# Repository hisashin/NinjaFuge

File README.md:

NinjaFuge
==========

Opensource ([CC BY-NC-SA 2.5](https://creativecommons.org/licenses/by-nc-sa/2.5/)) centrifuge with cover sensor and lock. Derived from [F.Lab's one](http://www.instructables.com/id/3D-Printed-DIYbio-Mini-Centrifuge/).

- [Frequently asked questions](#faq)
- [Changelog](#change)
- [Please note before making](#note)
- [Bill of material](#bom)
- [Wirings](#wire)
- [Source code](https://github.com/hisashin/NinjaFuge/blob/master/sourcecode/NinjaFuge/NinjaFuge.ino)
- [Assembly instructions](#assembly)

### FAQ

- How much?

	I made at $20 from junks. If you buy everythings new in Japan, total parts price is $75 now.

- How fast?

	Max 12,000RPM in my case by connecting 12V adapter to cheapest ($10) 1000KV (that means +1000RPM per 1V) motor. You can make it faster if you use higher voltage, faster motor or enough ampere. Do not exceed absolute maximum voltages of motor, ESC and microcontroller.

### Changelog

- 2017 Aug 7 : Changes from [F.Lab's one](http://www.instructables.com/id/3D-Printed-DIYbio-Mini-Centrifuge/)
	- Enclosure is changed from 3d printing to acrylic lasercut. because I think printing takes too long time and easier to get fail.
	- Added magnet to cover and reed switch to base. so that it can stop rorating when cover is opened.
- 2017 Aug 8 : Add safety lock
	- I don't know how to brake motor and it takes seconds to stop rorating. That means it's still not safe perfectly. 
	Small servo motor should be added to lock the cover while rotating.

### Notes before making

- Any hinge around you can be used but yours will not be same as mine. Don't forget to change holes on both cover_back and base_back to yours.
- Similar minor changes will be required for other parts like motor, variable resistor and switch. If you use bigger Arduino, basement should be wider.
- I used acrylic board, polycarbonate screws and nuts. If you want to proof it against rotor break, polycarbonate board, steel screws and [nylon nuts](https://en.wikipedia.org/wiki/Nyloc_nut) are recommended.

### Bill of material

- Lasercut 3mm acrylic or polycarbonate parts with [this](https://github.com/hisashin/NinjaFuge/blob/master/lasercut/NinjaFuge_3mm_clear.pdf).
- 3d printed [rotor](https://github.com/hisashin/NinjaFuge/blob/master/3dprint/stl/NinjaFuge_F.lab_Rotor.stl) and [motor base](https://github.com/hisashin/NinjaFuge/blob/master/3dprint/stl/NinjaFuge_motor_holder.stl) with any material.
- Some heat shrinkable tubes with different diameters are useful to protect solderings.
- Small microcontroller like [Arduino Nano](https://store.arduino.cc/usa/arduino-nano) ($22), [Arduino Pro Mini](http://www.sparkfun.com/products/11113) ($10) or anything you like. If you can make Arduino with [Arduino](https://www.arduino.cc/en/Tutorial/ArduinoISP) or [AVRISP mkII](http://www.atmel.com/tools/avrispmkii.aspx), single [ATmega328](https://www.digikey.jp/product-detail/ja/microchip-technology/ATMEGA328P-PU/ATMEGA328P-PU-ND/1914589) ($2.2) is enough. In any case, these pins are required.
	- 1 analog input for tune
	- 1 digital input to catch [interrupt](https://www.arduino.cc/en/Reference/AttachInterrupt) of reed switch
	- 2 digital output for ESC and door lock servo. VCC should be connected to them too. Refer [Wirings](#wire).
- Parts for enclosure
	- 29 M3 10mm screws
	- 8 M3 nuts
	- 4 M3 25mm spacer (both female) for base
	- 3 M3 100mm spacer (both female) for cover
	- To hold door lock servo, I used
		- 2 M2 8mm screws
		- 2 M2 nuts

- Are you living in Japan as me? Good. No need to change lasercut design if you use them.

	- [Brushless motor and ESC kit](https://www.amazon.co.jp/gp/product/B01MTCBO7D/ref=oh_aui_detailpage_o09_s00?ie=UTF8&psc=1)
	- [Small servo to lock door]()
	- [Variable resistor](http://akizukidenshi.com/catalog/g/gP-00246/)
	- [Nob for resistor](http://akizukidenshi.com/catalog/g/gP-00246/)
	- [Single circuit locker switch](https://www.sengoku.co.jp/mod/sgk_cart/detail.php?code=3A8K-4BFY)
	- [Neodymium magnet](http://www.sengoku.co.jp/mod/sgk_cart/detail.php?code=EEHD-4VZZ)
	- [Reed switch](http://akizukidenshi.com/catalog/g/gP-03676/)
	- [Hinge](https://hands.net/goods/4991807041906/)
	- [4 rubber foot if you want](http://www.sengoku.co.jp/mod/sgk_cart/detail.php?code=6AZE-JELC)
	- [DC jack](http://www.sengoku.co.jp/mod/sgk_cart/detail.php?code=EEHD-0HMZ)
	- [12V AC adapter](http://akizukidenshi.com/catalog/g/gM-06961/)
		- 5A looks well. 1A wasn't enough. If you need maximum RPM, check how much ampere your ESC needs.

- If not, it would be cheaper to find items similar to above list around you and move [holes](https://github.com/hisashin/NinjaFuge/blob/master/lasercut/NinjaFuge_3mm_clear.pdf) a little for each of them.

### Wirings

### Assembly instructions

- Need to make latest model from scratch taking photos or movies to document here. Anyone want to do that?

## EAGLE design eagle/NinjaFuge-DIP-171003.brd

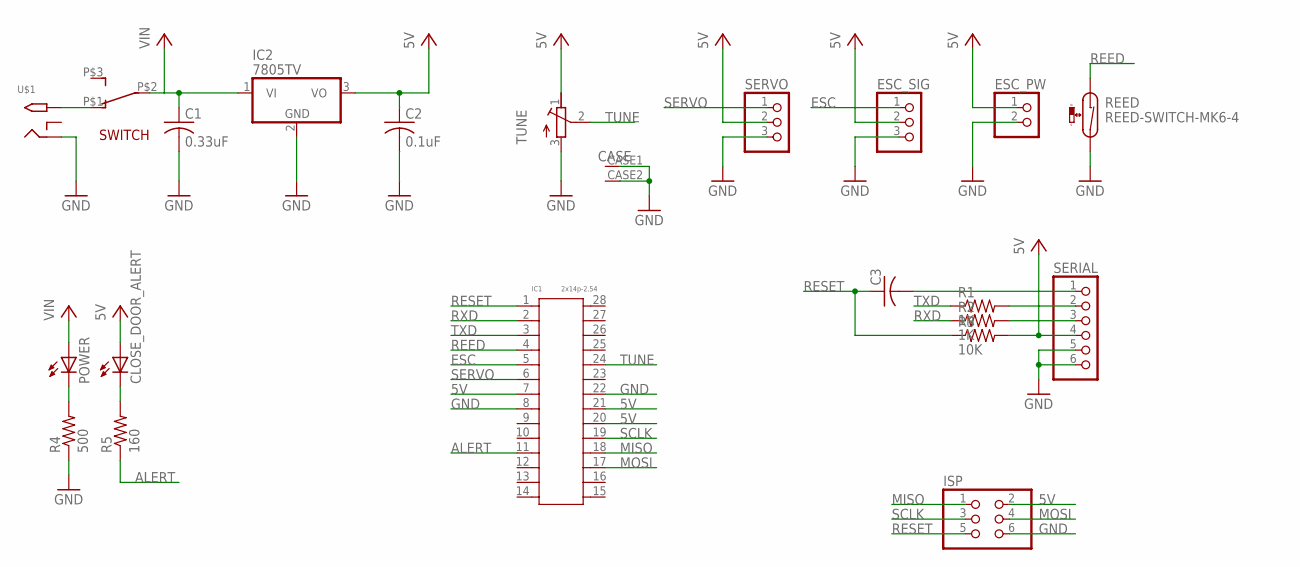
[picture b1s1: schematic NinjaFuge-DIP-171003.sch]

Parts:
C1: 0.33uF; C050-024X044
C2: 0.1uF; C050-024X044
C3: C-US050-024X044; C050-024X044
CLOSE_DOOR_ALERT: LED3MM
ESC_PW: PINHD-1X2; 1X02
ESC_SIG: PINHD-1X3; 1X03
IC1: 2x14p-2.54; SCK28-2.54-35.6X10MM
IC2: 7805TV; TO220V
ISP: PINHD-2X3; 2X03
POWER: LED3MM
R1, R2: 1K; 0204/5
R3: 10K; 0204/5
R4: 500; 0204/5
R5: 160; 0204/5
REED: REED-SWITCH-MK6-4; MK6-4
SERIAL: PINHD-1X6; 1X06
SERVO: PINHD-1X3; 1X03
SWITCH: MARUSHIN_MSR5
TUNE: RK09D117000B
U$1: 2.1MMJACKTHM; PJ-102A

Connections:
5V: C2.1, CLOSE_DOOR_ALERT.A, ESC_SIG.2, IC1.7, IC1.20, IC1.21, IC2.3 (VO), ISP.2, R3.2, SERIAL.4, SERVO.2, TUNE.1
ALERT: IC1.11, R5.1
ESC: ESC_SIG.1, IC1.5
GND: C1.2, C2.2, ESC_PW.2, ESC_SIG.3, IC1.8, IC1.22, IC2.2 (GND), ISP.6, R4.1, REED.2, SERIAL.5, SERIAL.6, SERVO.3, TUNE.3, TUNE.CASE1, TUNE.CASE2, U$1.RING
MISO: IC1.18, ISP.1
MOSI: IC1.17, ISP.4
unnamed: SWITCH.P$1 (1), U$1.TIP
unnamed: R2.2, SERIAL.3
unnamed: R1.2, SERIAL.2
unnamed: POWER.K (C), R4.2
unnamed: C3.2, SERIAL.1
unnamed: CLOSE_DOOR_ALERT.K (C), R5.2
REED: IC1.4, REED.1
RESET: C3.1, IC1.1, ISP.5, R3.1
RXD: IC1.2, R2.1
SCLK: IC1.19, ISP.3
SERVO: IC1.6, SERVO.1
TUNE: IC1.24, TUNE.2
TXD: IC1.3, R1.1
VIN: C1.1, ESC_PW.1, IC2.1 (VI), POWER.A, SWITCH.P$2 (2)

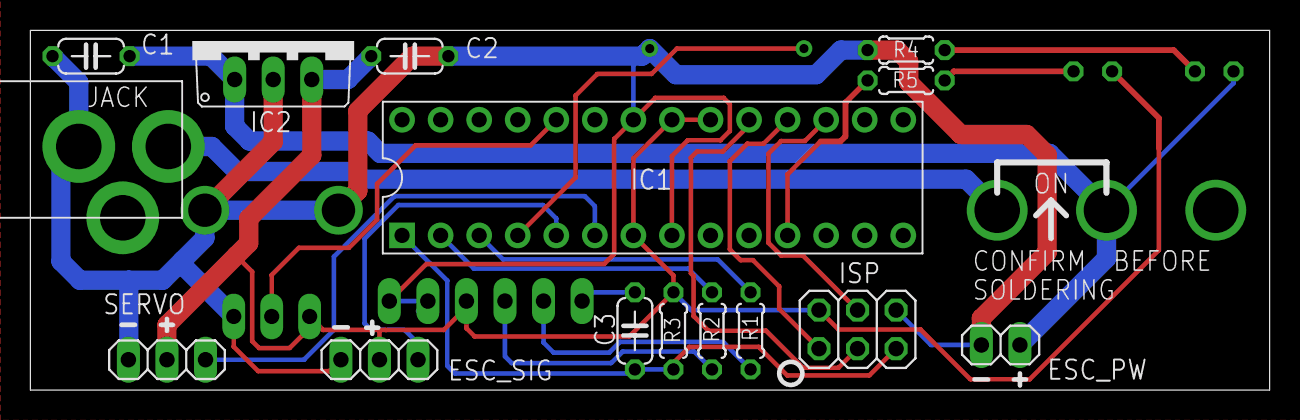
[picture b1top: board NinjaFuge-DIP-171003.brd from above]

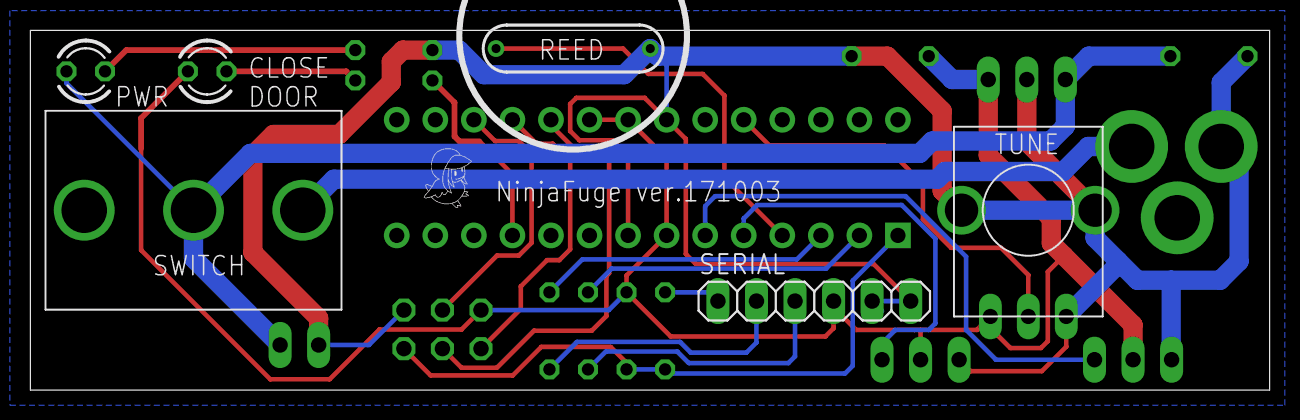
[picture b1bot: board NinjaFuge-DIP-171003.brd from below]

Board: 2 copper layers, 81.7 x 23.7 mm, 22 parts (7 on the bottom side), 20 nets.

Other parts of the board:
U$2: TORI_0.125

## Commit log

2017-08-07 move dir
2017-08-07 add diagram
2017-08-07 update diagram
2017-08-07 door lock added
2017-08-08 update md
2017-08-09 update lasercut
2017-08-09 update markdown
2017-08-09 update source
2017-08-11 add logo to exist pdf and nologo
2017-09-29 fixing things
2017-10-03 add pcb
2017-10-09 ordered pcb
2017-11-28 added another reed to check lock is locked or just hitting the wall
